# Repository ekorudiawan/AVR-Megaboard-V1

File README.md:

# AVR-Megaboard-V1
AVR Megaboard V1

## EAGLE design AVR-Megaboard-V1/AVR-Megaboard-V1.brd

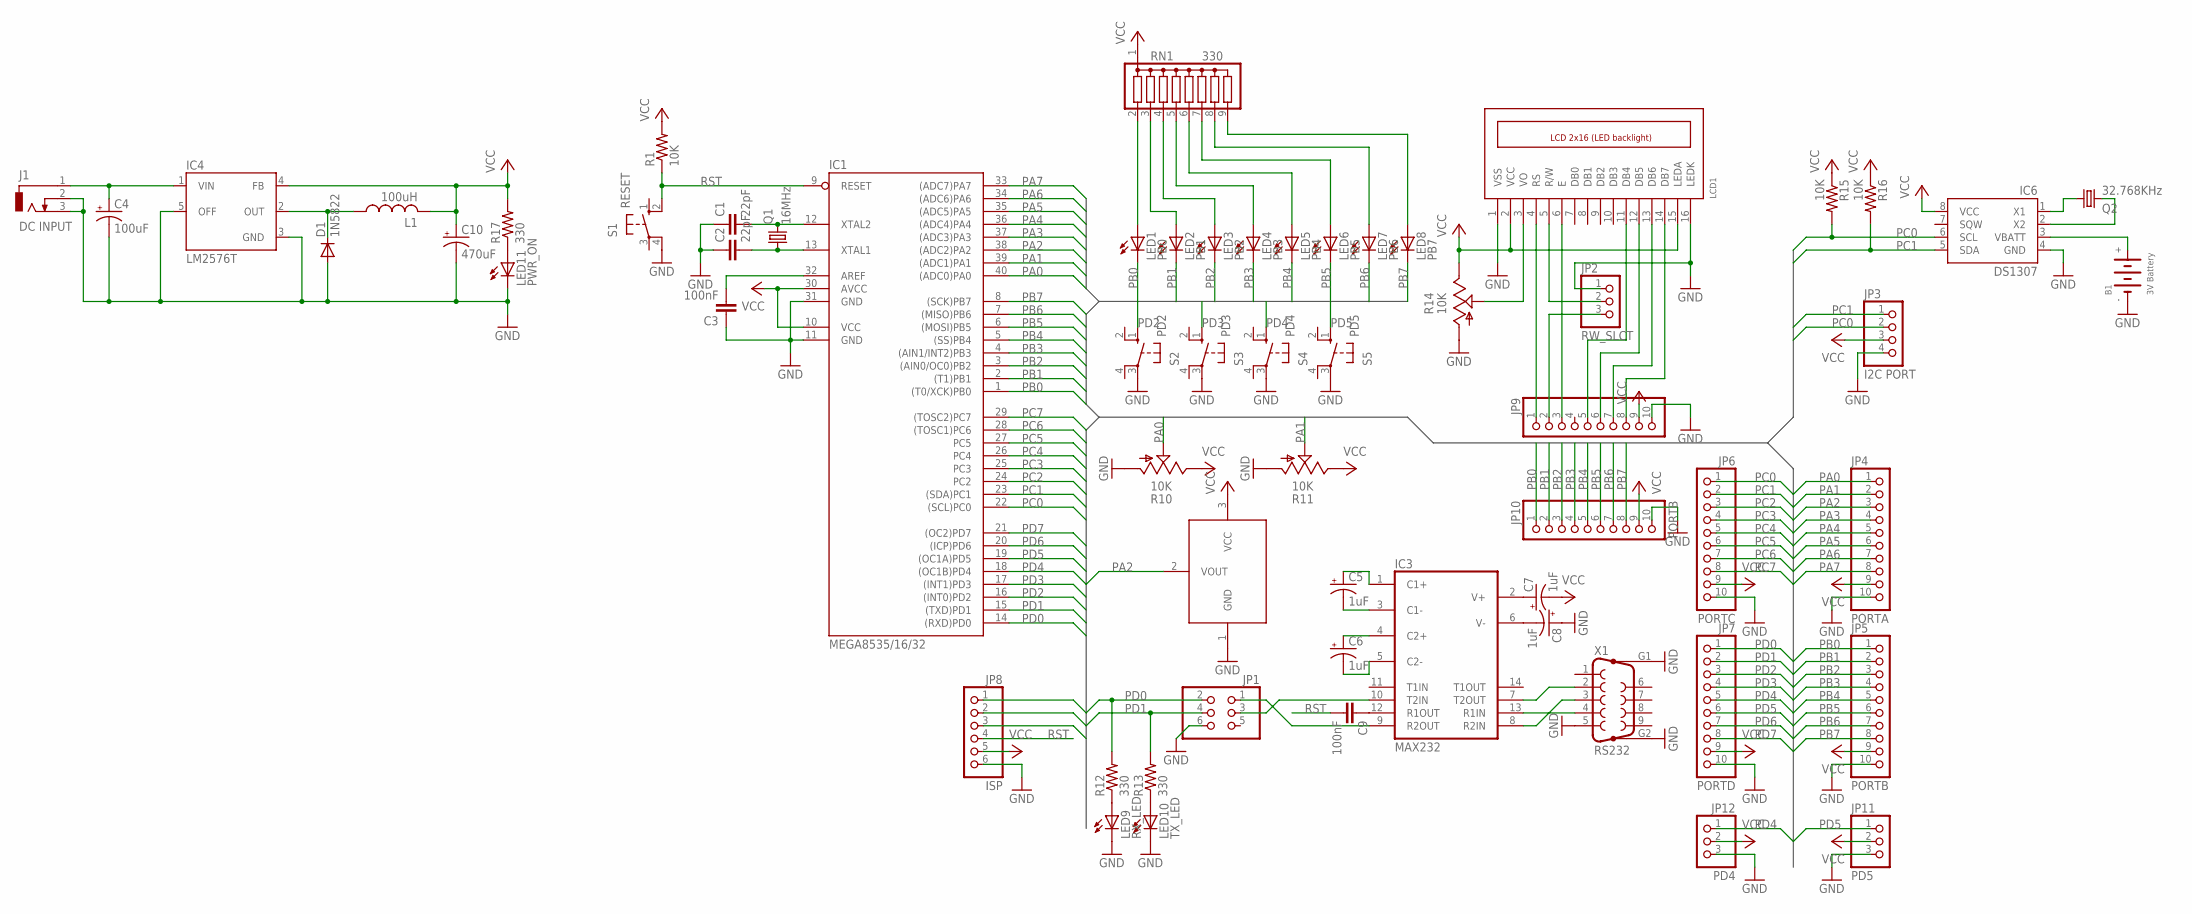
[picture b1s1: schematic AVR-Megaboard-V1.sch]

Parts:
B1: 3V Battery; CR2032
C1, C2: 22pF; C025-024X044
C3, C9: 100nF; C025-024X044
C4: 100uF; E2,5-6
C5, C6, C7, C8: 1uF; E2-4
C10: 470uF; E3,5-8
D1: 1N5822; DO201-15
IC1: MEGA8535/16/32; DIL40
IC2: LM35; TO92
IC3: MAX232; DIL16
IC4: LM2576T; TO220-5
IC6: DS1307; DIP08
J1: DC INPUT; DCJ0202
JP1: PINHD-2X3; 2X03
JP2: RW_SLCT; 1X03
JP3: I2C PORT; 1X04
JP4: PORTA; 1X10
JP5, JP10: PORTB; 1X10
JP6: PORTC; 1X10
JP7: PORTD; 1X10
JP8: ISP; 1X06
JP9: PINHD-1X10; 1X10
JP11: PD5; 1X03
JP12: PD4; 1X03
L1: 100uH; TJ3-U2
LCD1: LCD_2X16; HY-1602F
LED1: PB0; LED3MM
LED2: PB1; LED3MM
LED3: PB2; LED3MM
LED4: PB3; LED3MM
LED5: PB4; LED3MM
LED6: PB5; LED3MM
LED7: PB6; LED3MM
LED8: PB7; LED3MM
LED9: RX_LED; LED3MM
LED10: TX_LED; LED3MM
LED11: PWR_ON; LED3MM
Q1: 16MHz; HC49/S
Q2: 32.768KHz; TC26H
R1, R15, R16: 10K; 0207/10
R10, R11, R14: 10K; CA6V
R12, R13: 330; 0207/5V
R17: 330; 0207/2V
RN1: 330; SIL9
S1: RESET; B3F-10XX
S2: PD2; B3F-10XX
S3: PD3; B3F-10XX
S4: PD4; B3F-10XX
S5: PD5; B3F-10XX
X1: RS232; F09HP

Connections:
GND: B1.-, C1.1, C2.1, C3.1, C4.-, C8.+, C10.-, D1.A, IC1.11 (GND), IC1.31 (GND), IC2.1 (GND), IC3.15 (GND), IC4.3 (GND), IC4.5 (OFF), IC6.4 (GND), J1.2, J1.3, JP1.6, JP2.1, JP3.4, JP4.10, JP5.10, JP6.10, JP7.10, JP8.6, JP9.10, JP10.10, JP11.3, JP12.3, LCD1.1 (VSS), LCD1.16 (LEDK), LED9.K (C), LED10.K (C), LED11.K (C), R10.A, R11.A, R14.A, S1.4 (P1), S2.3, S3.3, S4.3, S5.3, X1.5, X1.G1, X1.G2
unnamed: C1.2, IC1.12 (XTAL2), Q1.2
unnamed: C2.2, IC1.13 (XTAL1), Q1.1
unnamed: C3.2, IC1.32 (AREF)
unnamed: C4.+, IC4.1 (VIN), J1.1
unnamed: LED1.A, RN1.2
unnamed: LED2.A, RN1.3
unnamed: LED3.A, RN1.4
unnamed: LED4.A, RN1.5
unnamed: LED5.A, RN1.6
unnamed: LED6.A, RN1.7
unnamed: LED7.A, RN1.8
unnamed: LED8.A, RN1.9
unnamed: IC3.13 (R1IN), X1.4
unnamed: C9.1, IC3.12 (R1OUT)
unnamed: IC3.10 (T2IN), JP1.3
unnamed: IC3.9 (R2OUT), JP1.1
unnamed: C5.-, IC3.3 (C1-)
unnamed: C6.+, IC3.4 (C2+)
unnamed: C5.+, IC3.1 (C1+)
unnamed: C6.-, IC3.5 (C2-)
unnamed: C7.+, IC3.2 (V+)
unnamed: C8.-, IC3.6 (V-)
unnamed: IC3.7 (T2OUT), X1.2
unnamed: IC3.8 (R2IN), X1.3
unnamed: LED9.A, R12.1
unnamed: LED10.A, R13.1
unnamed: LCD1.3 (VO), R14.S
unnamed: JP2.2, LCD1.5 (R/W)
unnamed: IC6.1 (X1), Q2.1
unnamed: IC6.2 (X2), Q2.2
unnamed: B1.+, IC6.3 (VBATT)
unnamed: D1.C, IC4.2 (OUT), L1.1
unnamed: LED11.A, R17.1
unnamed: JP9.1, LCD1.4 (RS)
unnamed: JP9.3, LCD1.6 (E)
unnamed: JP9.5, LCD1.11 (DB4)
unnamed: JP9.6, LCD1.12 (DB5)
unnamed: JP9.7, LCD1.13 (DB6)
unnamed: JP9.8, LCD1.14 (DB7)
unnamed: JP2.3, JP9.2
PA0: IC1.40 ((ADC0)PA0), JP4.1, R10.S
PA1: IC1.39 ((ADC1)PA1), JP4.2, R11.S
PA2: IC1.38 ((ADC2)PA2), IC2.2 (VOUT), JP4.3
PA3: IC1.37 ((ADC3)PA3), JP4.4
PA4: IC1.36 ((ADC4)PA4), JP4.5
PA5: IC1.35 ((ADC5)PA5), JP4.6
PA6: IC1.34 ((ADC6)PA6), JP4.7
PA7: IC1.33 ((ADC7)PA7), JP4.8
PB0: IC1.1 ((T0/XCK)PB0), JP5.1, JP10.1, LED1.K (C)
PB1: IC1.2 ((T1)PB1), JP5.2, JP10.2, LED2.K (C)
PB2: IC1.3 ((AIN0/OC0)PB2), JP5.3, JP10.3, LED3.K (C)
PB3: IC1.4 ((AIN1/INT2)PB3), JP5.4, JP10.4, LED4.K (C)
PB4: IC1.5 ((SS)PB4), JP5.5, JP10.5, LED5.K (C)
PB5: IC1.6 ((MOSI)PB5), JP5.6, JP8.1, JP10.6, LED6.K (C)
PB6: IC1.7 ((MISO)PB6), JP5.7, JP8.2, JP10.7, LED7.K (C)
PB7: IC1.8 ((SCK)PB7), JP5.8, JP8.3, JP10.8, LED8.K (C)
PC0: IC1.22 ((SCL)PC0), IC6.6 (SCL), JP3.2, JP6.1, R15.2
PC1: IC1.23 ((SDA)PC1), IC6.5 (SDA), JP3.1, JP6.2, R16.2
PC2: IC1.24 (PC2), JP6.3
PC3: IC1.25 (PC3), JP6.4
PC4: IC1.26 (PC4), JP6.5
PC5: IC1.27 (PC5), JP6.6
PC6: IC1.28 ((TOSC1)PC6), JP6.7
PC7: IC1.29 ((TOSC2)PC7), JP6.8
PD0: IC1.14 ((RXD)PD0), JP1.2, JP7.1, R12.2
PD1: IC1.15 ((TXD)PD1), JP1.4, JP7.2, R13.2
PD2: IC1.16 ((INT0)PD2), JP7.3, S2.1 (S)
PD3: IC1.17 ((INT1)PD3), JP7.4, S3.1 (S)
PD4: IC1.18 ((OC1B)PD4), JP7.5, JP12.1, S4.1 (S)
PD5: IC1.19 ((OC1A)PD5), JP7.6, JP11.1, S5.1 (S)
PD6: IC1.20 ((ICP)PD6), JP7.7
PD7: IC1.21 ((OC2)PD7), JP7.8
RST: C9.2, IC1.9 (RESET), JP8.4, R1.1, S1.2 (S1)
VCC: C7.-, C10.+, IC1.10 (VCC), IC1.30 (AVCC), IC2.3 (VCC), IC3.16 (VCC), IC4.4 (FB), IC6.8 (VCC), JP3.3, JP4.9, JP5.9, JP6.9, JP7.9, JP8.5, JP9.9, JP10.9, JP11.2, JP12.2, L1.2, LCD1.2 (VCC), LCD1.15 (LEDA), R1.2, R10.E, R11.E, R14.E, R15.1, R16.1, R17.2, RN1.1

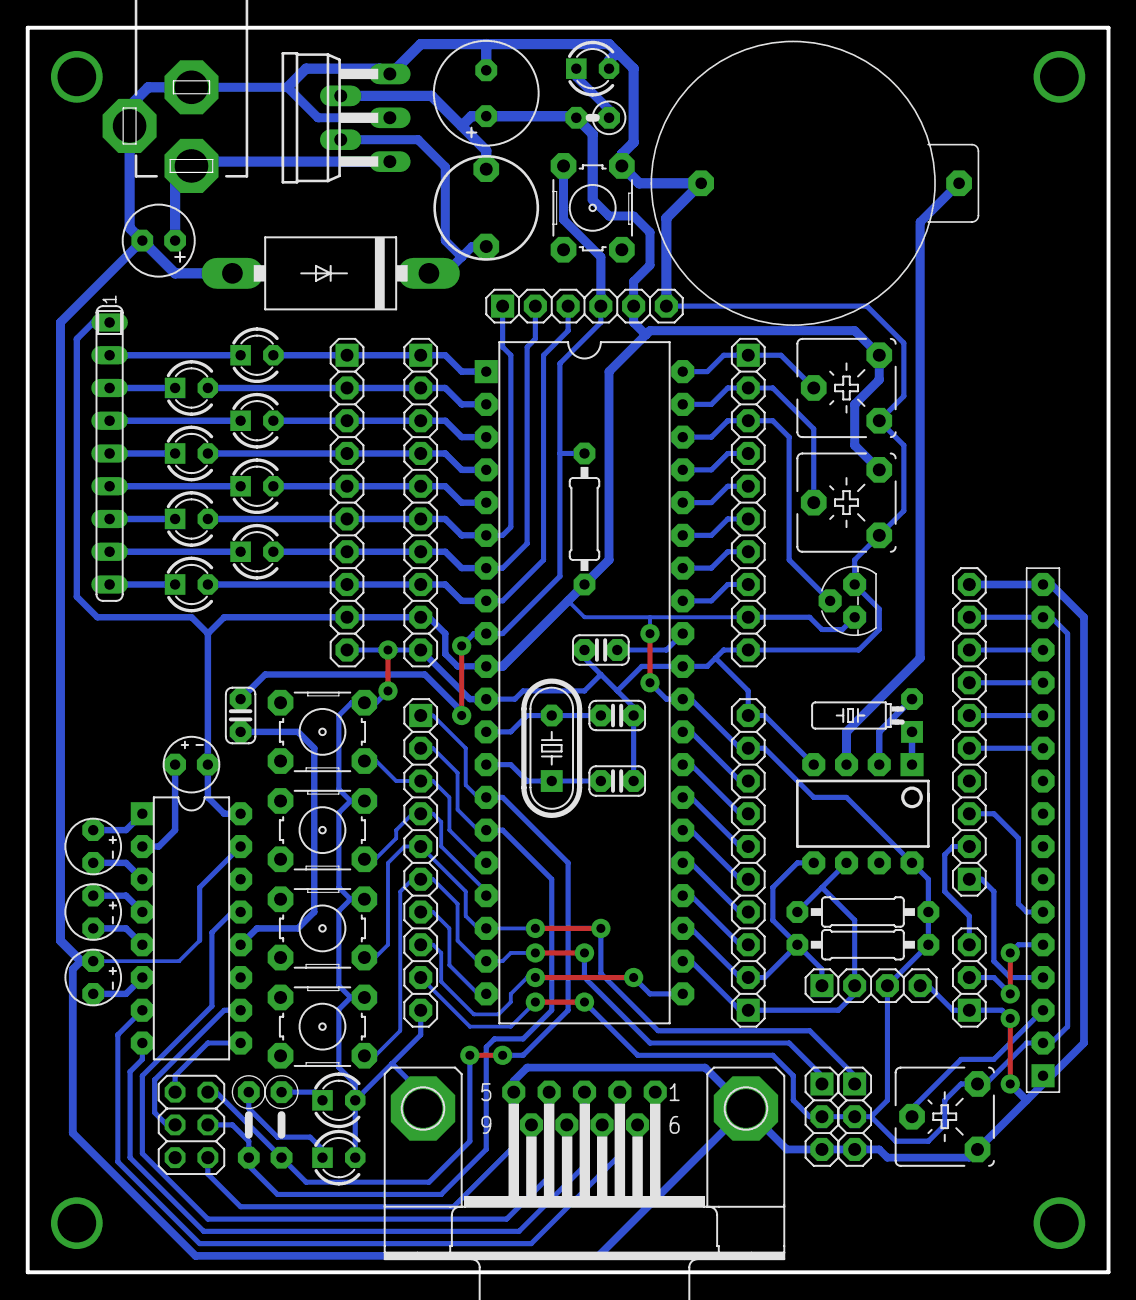
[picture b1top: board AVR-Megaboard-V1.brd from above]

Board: 2 copper layers, 83.8 x 96.5 mm, 61 parts (0 on the bottom side), 75 nets.

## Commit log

2017-10-03 Added Source Files
